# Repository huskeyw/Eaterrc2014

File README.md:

# Eaterrc2014
Building a Ben Eater 8 bit bread board like computer using the RC2014 back place 

So far the Clock Diagram and added to Clock and Clock 2 of the bus
Need to Compleate the other modules. I believe I should be able to use the RC2014 64K ram board and maybe some others..

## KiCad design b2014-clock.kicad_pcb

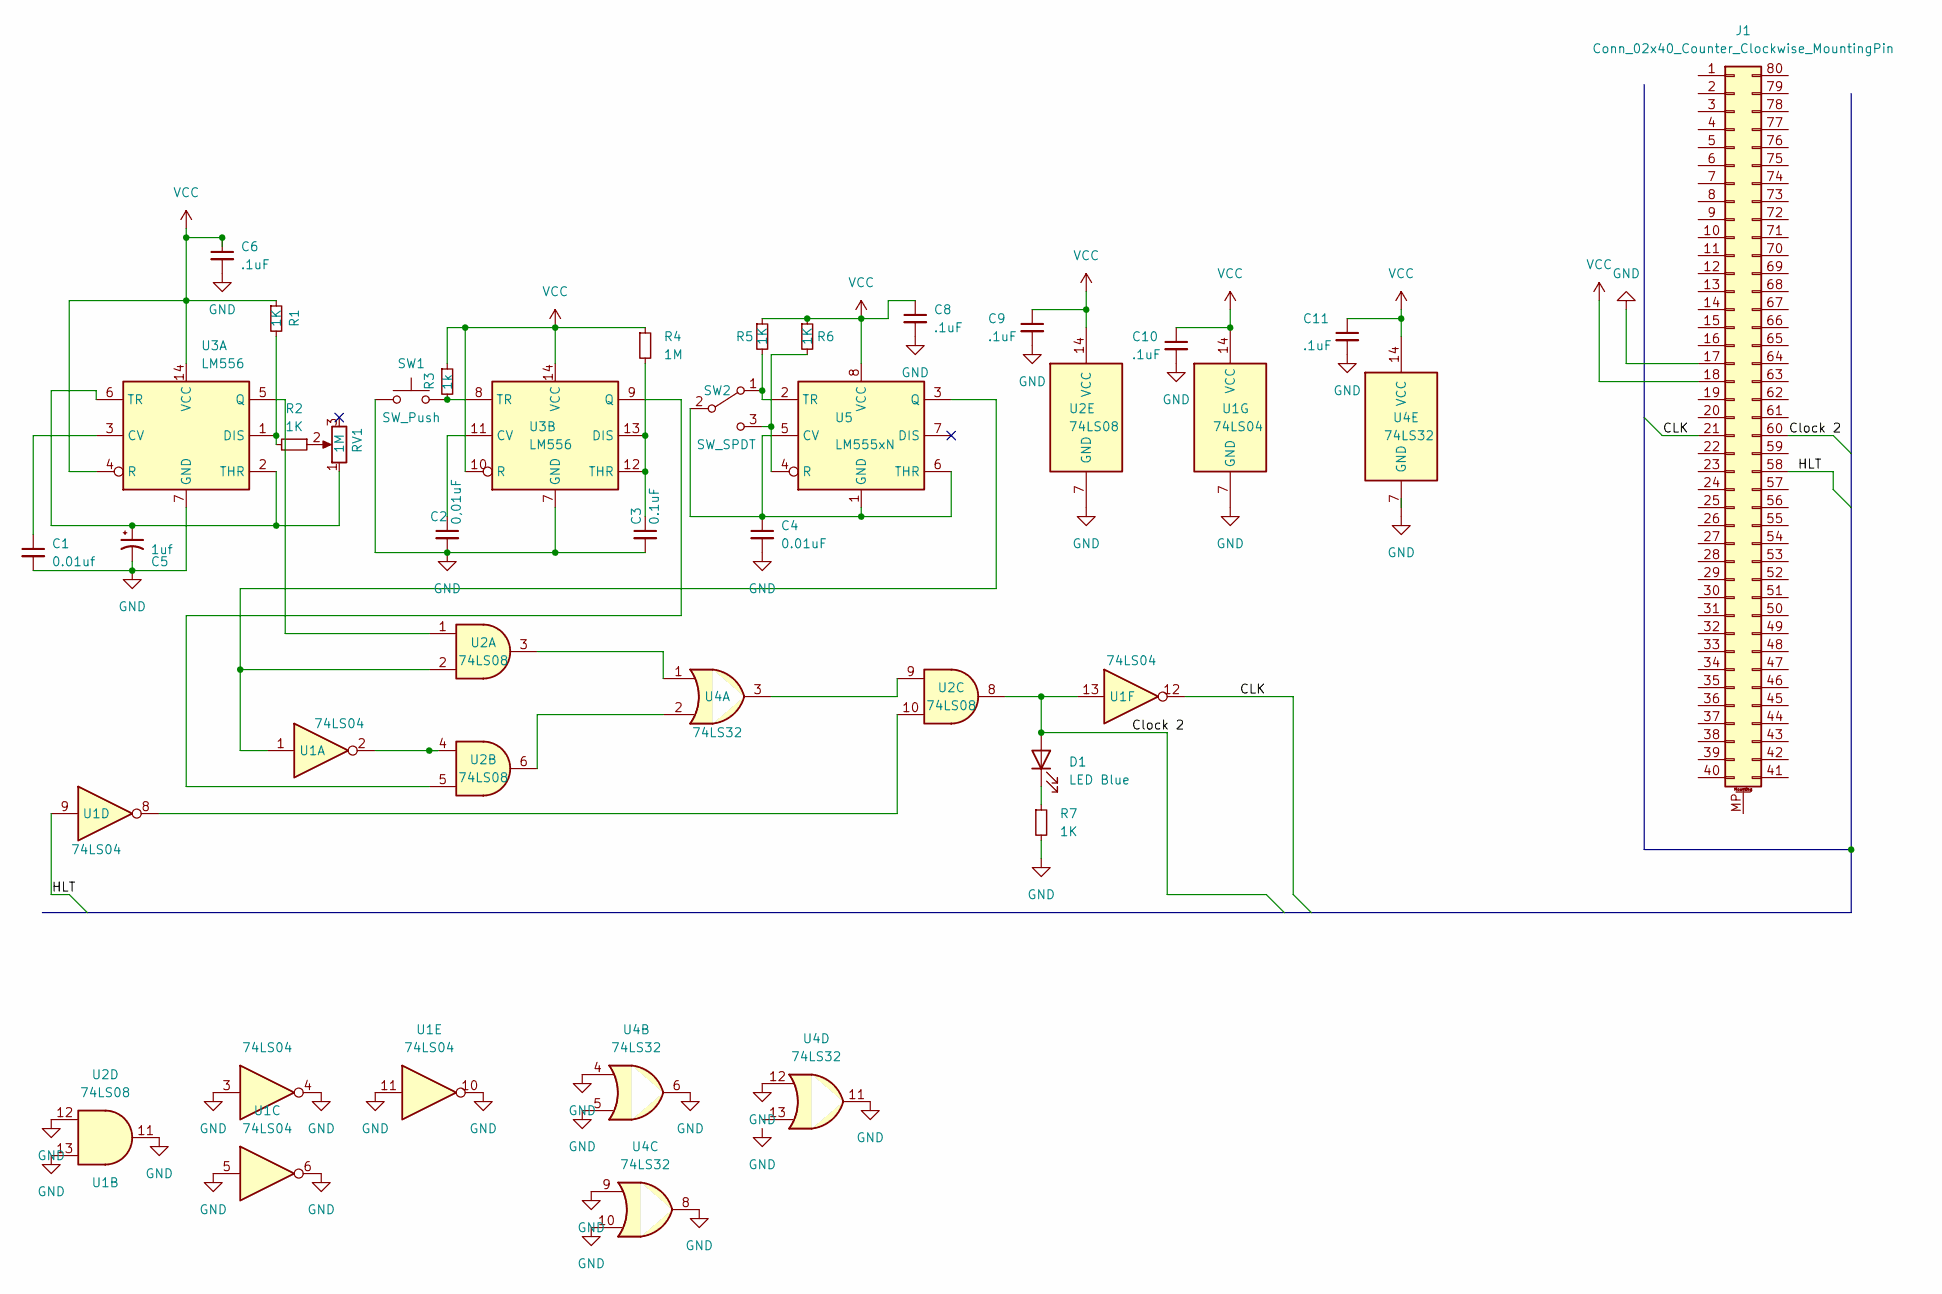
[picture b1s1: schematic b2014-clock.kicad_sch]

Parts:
C1: 0.01uf; C_Disc_D3.0mm_W2.0mm_P2.50mm
C2: 0,01uF; C_Disc_D3.0mm_W2.0mm_P2.50mm
C3: 0.1uF; C_Disc_D3.0mm_W2.0mm_P2.50mm
C4: 0.01uF; C_Disc_D3.0mm_W2.0mm_P2.50mm
C5: 1uf; CP_Radial_D4.0mm_P2.00mm
C6, C8, C9, C10, C11: .1uF; C_Disc_D3.0mm_W2.0mm_P2.50mm
D1: LED Blue; LED_D3.0mm
J1: Conn_02x40_Counter_Clockwise_MountingPin
R1, R2, R5, R6, R7: 1K; R_Axial_DIN0204_L3.6mm_D1.6mm_P5.08mm_Horizontal
R3: 1k; R_Axial_DIN0204_L3.6mm_D1.6mm_P5.08mm_Horizontal
R4: 1M; R_Axial_DIN0204_L3.6mm_D1.6mm_P5.08mm_Horizontal
RV1: 1M; Potentiometer_ACP_CA6-H2,5_Horizontal
SW1: SW_Push; SW_Tactile_Straight_KSA0Axx1LFTR
SW2: SW_SPDT; KSA_Tactile_SPST
U1: 74LS04; DIP-14_W7.62mm_LongPads
U2: 74LS08; DIP-14_W7.62mm_LongPads
U3: LM556; DIP-14_W7.62mm
U4: 74LS32; DIP-14_W7.62mm_LongPads
U5: LM555xN; DIP-8_W7.62mm

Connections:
/CLK: J1.21, U1.12
/Clock 2: D1.2 (A), J1.60, U1.13, U2.8
/HLT: J1.58, U1.9
GND: C1.2, C2.2, C3.2, C4.2, C5.2, C6.2, C8.2, C9.2, C10.2, C11.2, J1.17, R7.2, SW1.1, U1.3, U1.4, U1.5, U1.6, U1.7 (GND), U1.10, U1.11, U2.7 (GND), U2.11, U2.12, U2.13, U3.7 (GND), U4.4, U4.5, U4.6, U4.7 (GND), U4.8, U4.9, U4.10, U4.11, U4.12
unnamed: D1.1 (K), R7.1
unnamed: R1.2, R2.2, U3.1 (DIS)
unnamed: R3.2, SW1.2, U3.8 (TR)
unnamed: C3.1, R4.2, U3.12 (THR), U3.13 (DIS)
unnamed: R5.2, SW2.1 (A), U5.2 (TR)
unnamed: R6.2, SW2.3 (C), U5.4 (R)
unnamed: R2.1, RV1.2
unnamed: U2.1, U3.5 (Q)
unnamed: U1.1, U2.2, U5.3 (Q)
unnamed: U2.3, U4.1
unnamed: U1.2, U2.4
unnamed: U2.5, U3.9 (Q)
unnamed: U2.6, U4.2
unnamed: U2.9, U4.3
unnamed: U1.8, U2.10
unnamed: C1.1, U3.3 (CV)
unnamed: C5.1, RV1.1, U3.2 (THR), U3.6 (TR)
unnamed: C2.1, U3.11 (CV)
unnamed: C4.1, SW2.2 (B), U5.1 (GND), U5.5 (CV), U5.6 (THR)
VCC: C6.1, C8.1, C9.1, C10.1, C11.1, J1.18, R1.1, R3.1, R4.1, R5.1, R6.1, U1.14 (VCC), U2.14 (VCC), U3.4 (R), U3.10 (R), U3.14 (VCC), U4.14 (VCC), U5.8 (VCC)

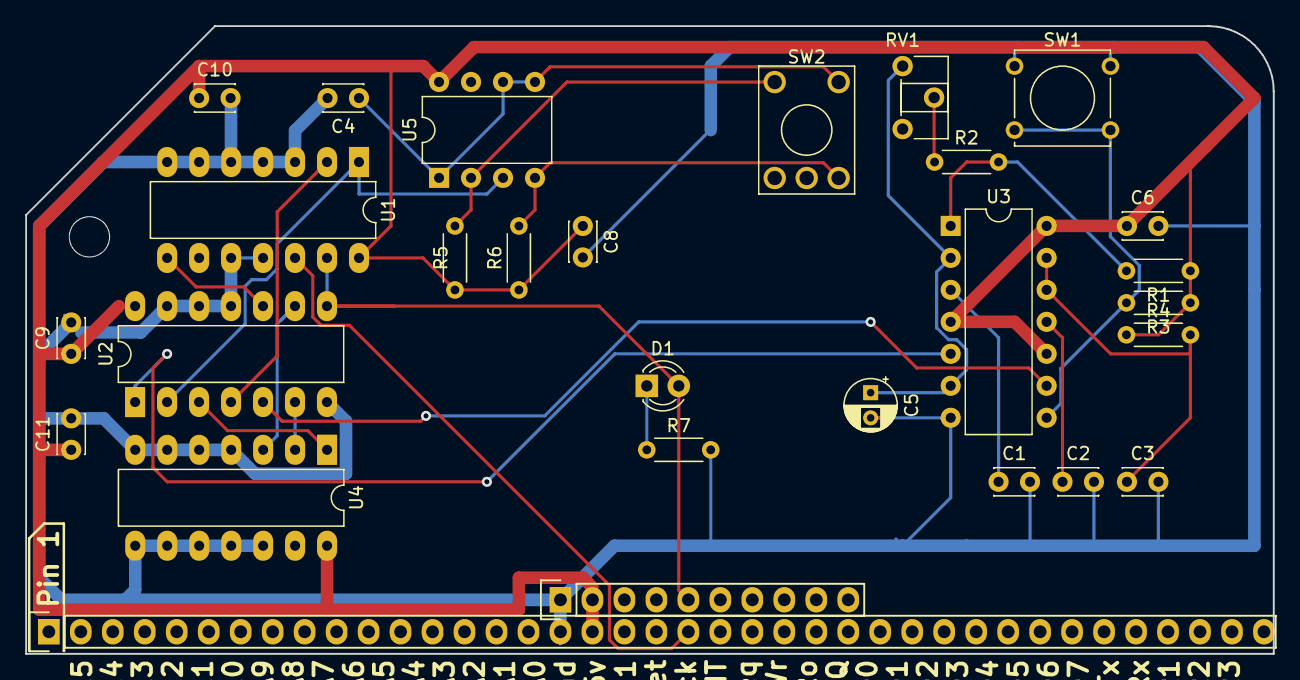
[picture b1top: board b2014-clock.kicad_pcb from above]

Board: 2 copper layers, 99.1 x 49.9 mm, 26 parts (0 on the bottom side), 22 nets.
